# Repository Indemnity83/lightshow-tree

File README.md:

# lightshow-tree

Firmware and hardware notes for adapting a Member's Mark Pre-Lit Multicolor
Lightshow Tree to a Falcon differential output.

The first target retains the tree's factory power board, connector harness, and
30 vertical WS28xx data paths. Two Falcon differential pixel outputs carry the
1,020 vertical pixels, 510 each; two small on-board RS-485 receivers convert
them to the STC MCU's 3.3 V input level.

## Status

The pixel-output mapping is confirmed, and the two-channel receiver drives all
30 verticals from two Falcon outputs: a Falcon chase test runs cleanly across
the seam between verticals 15 and 16. The power limiter holds full white
at about 1.24 A from the factory 1.6 A supply. The star and a fourth output are
deferred (see the hardware plan).

| Target | Purpose |
| --- | --- |
| `blank` | Drives all 31 pixel-data pins low (WS28xx idle); safe first flash |
| `mapper` | Lights one of the 31 outputs dim red; the button steps to the next |
| `color-test` | Whole tree dim red, green, or blue; the button cycles the color |
| `demo` | Red/green/blue spiral bands; the button rotates them |
| `probe` | Reports activity and polarity on the three former radio pads |
| `receiver` | Two-channel Falcon receiver |

## Layout

- `docs/` — confirmed board mapping, open questions, and ISP procedure
- `include/` — board-level declarations
- `src/` — firmware source
- `scripts/` — local development helpers

## Toolchain

The project targets the STC8H8K64U (8051-compatible) MCU.

- [SDCC](https://sdcc.sourceforge.net/) compiles the firmware.
- [stc8prog](https://github.com/IOsetting/stc8prog) detects and flashes the MCU
  over UART on macOS.

Once both are installed:

```sh
make
make blank
make mapper
make receiver
make probe
make check-toolchain
make detect PORT=/dev/cu.usbserial-XXXX
make flash-receiver PORT=/dev/cu.usbserial-XXXX
make terminal PORT=/dev/cu.usbserial-XXXX
```

`make detect` is non-destructive. See `docs/isp.md` before running it.
Exit the serial terminal with `Ctrl-A`, then `\\`.

The local `tools/stc8prog/` checkout is ignored by Git. It is the default
flashing tool while developing on this Mac; a globally installed copy can be
selected with `make STC8PROG=stc8prog ...`.

See [the hardware plan](docs/hardware-plan.md) for the selected MAX3485 and
base-mounted RJ45 breakout modules, wiring, and Falcon pair selection.

## Falcon receiver bring-up

`make receiver` builds the RS-485 receiver firmware. It samples two MAX3485
`RXD` outputs at once: channel 1 on STC pin 27 / P3.6 (verticals 1–15) and
channel 2 on STC pin 29 / P4.1 (verticals 16–30). Each channel is one
510-pixel RGB Falcon output; this tree uses Falcon ports 29 and 30. The
firmware replays the frame in the confirmed clockwise order. Brightness is
set by the Falcon port; the firmware only scales a frame down if its
estimated draw would exceed the power supply budget.

Flash it only with each MAX3485 configured receive-only (`T` open, `EN` low or
open, `TXD` unconnected). Use `make flash-probe` first to confirm each pad
sees its own correctly polarized signal. The first valid capture emits
`frame: captured and replayed` on the UART. See `docs/receiver.md` for the
bring-up procedure, troubleshooting, and the sampling delay.

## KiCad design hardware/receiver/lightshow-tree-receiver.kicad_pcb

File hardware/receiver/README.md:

# Lightshow Tree Differential Receiver Daughterboard

This KiCad project will hold a small, castellated daughterboard installed on
the pads exposed by removing the factory PAN2110P0AA radio.  Its function is to
receive Falcon differential data feeds and deliver logic-level signals to the
existing STC8H8K64U.

The current KiCad design receives one feed.  The tree now needs two (510
pixels each, see `docs/hardware-plan.md`): channel 1 on GPIO 27 / pad 3 and
channel 2 on GPIO 29 / pad 1.  A future revision duplicates the receiver
circuit for the second channel.  The STC firmware then produces the 30
independent pixel outputs already proven on the factory board.

## Important constraint

The former radio pads provide a particularly useful three-wire interface.  The
factory firmware used the following three pins for the radio protocol, but our
replacement firmware can repurpose any one of them as a receiver-data GPIO:

| STC pin | Radio pin | Factory-radio function | Daughterboard use |
| --- | --- | --- | --- |
| 27 | 3 | data/SDA | channel 1 receiver data |
| 28 | 2 | clock/SCL | spare GPIO |
| 29 | 1 | chip select | channel 2 receiver data |

In addition, the radio footprint exposes its local 3.3 V and ground pads.  The
daughterboard will solder to exactly three factory pads: 3.3 V, ground, and the
chosen GPIO.  The factory radio's other pads are deliberately left unconnected
on the daughterboard.

The established UART pads remain useful only for development/debugging:

| Factory net | STC pin | Development use |
| --- | --- | --- |
| T2 / J1-2 | 19, P3.0 UART RX | ISP/programming |
| T3 / J1-6 | 20, P3.1 UART TX | optional debug output |
| 3.3 V test pad | 15, VCC | alternate measurement point |
| T4 | 17, GND | alternate measurement point |

The castellated edge therefore provides both the mechanical mounting and the
complete run-time electrical interface.  Revision 1 should still include
unpopulated debug pads for its input and ground, rather than a permanent wire
to T2/T3.

## First-revision functional blocks

1. Falcon differential-pair input connector/pads.
2. 3.3 V RS-485/RS-422 receiver with a valid high-speed logic output.
3. Logic connection to STC GPIO 27 (factory radio pin 3), with alternatives
   available on GPIO 28 and GPIO 29 if placement makes another pad preferable.
4. 3.3 V decoupling, input protection/termination option, and ground return.
5. Castellated mechanical edges, sized only after measuring the removed radio
   footprint and available clearances.

## Measurements still required before layout

- Exact PAN2110P0AA footprint dimensions and orientation on the factory PCB.
- Maximum safe daughterboard outline to the left of that footprint.
- Which Falcon differential pair/pairs will be connected and the physical
  connector/cable plan.
- Differential signalling details from the Falcon port: line rate, pair
  assignment, and whether a termination resistor is already present upstream.

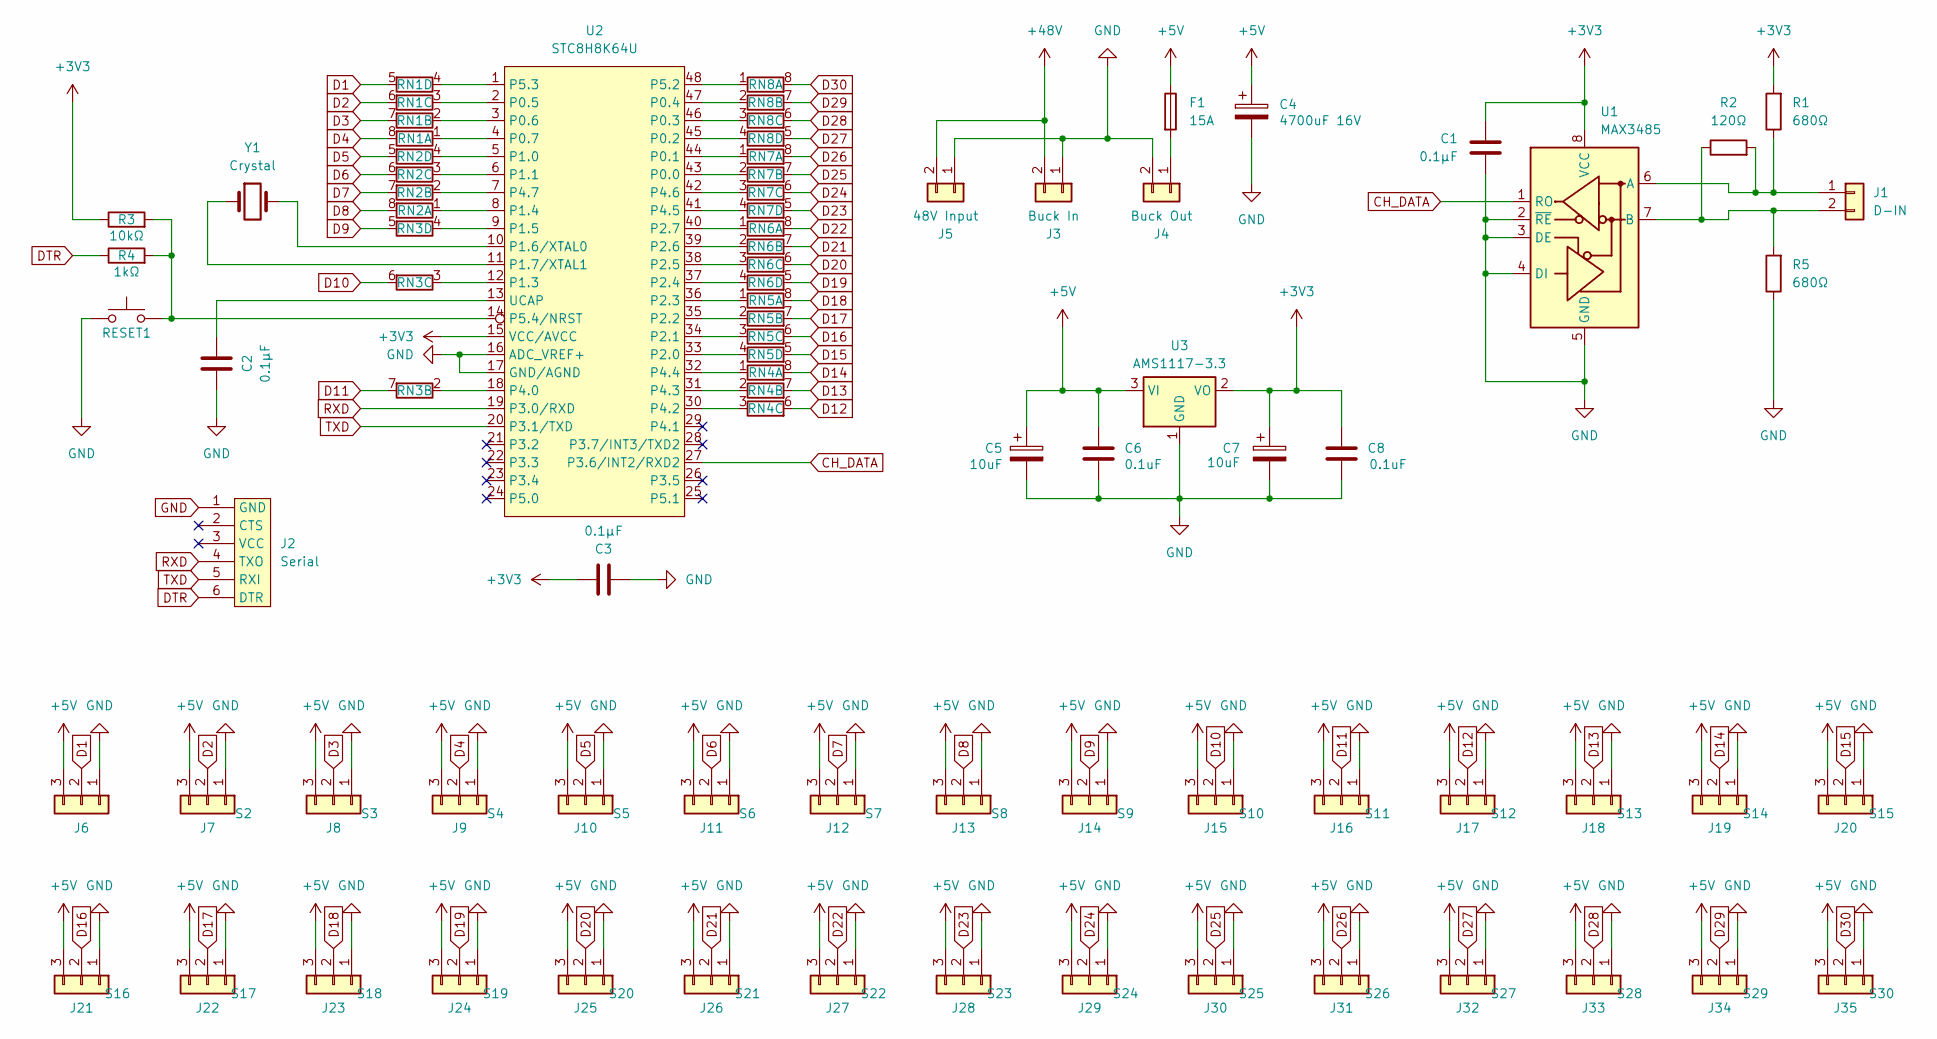
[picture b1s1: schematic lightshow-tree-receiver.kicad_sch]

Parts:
C1, C2, C3: 0.1µF; C_0805_2012Metric
C4: 4700uF 16V; CP_Radial_D16.0mm_P7.50mm
C5, C7: 10uF; CP_Radial_D5.0mm_P2.00mm
C6, C8: 0.1uF; C_0805_2012Metric
F1: 15A; Fuseholder_Blade_Mini_Keystone_3568
J1: D-IN; WirePads_1x02_P3.50mm_CAT5_6
J2: Serial; PinSocket_1x06_P2.54mm_Vertical
J3: Buck In; WirePads_1x02_P7.62mm_14AWG
J4: Buck Out; WirePads_1x02_P7.62mm_14AWG
J5: 48V Input; WirePads_1x02_P7.62mm_14AWG
J6: S1; WirePads_1x03_P2.20mm_FlatPixelWire
J7: S2; WirePads_1x03_P2.20mm_FlatPixelWire
J8: S3; WirePads_1x03_P2.20mm_FlatPixelWire
J9: S4; WirePads_1x03_P2.20mm_FlatPixelWire
J10: S5; WirePads_1x03_P2.20mm_FlatPixelWire
J11: S6; WirePads_1x03_P2.20mm_FlatPixelWire
J12: S7; WirePads_1x03_P2.20mm_FlatPixelWire
J13: S8; WirePads_1x03_P2.20mm_FlatPixelWire
J14: S9; WirePads_1x03_P2.20mm_FlatPixelWire
J15: S10; WirePads_1x03_P2.20mm_FlatPixelWire
J16: S11; WirePads_1x03_P2.20mm_FlatPixelWire
J17: S12; WirePads_1x03_P2.20mm_FlatPixelWire
J18: S13; WirePads_1x03_P2.20mm_FlatPixelWire
J19: S14; WirePads_1x03_P2.20mm_FlatPixelWire
J20: S15; WirePads_1x03_P2.20mm_FlatPixelWire
J21: S16; WirePads_1x03_P2.20mm_FlatPixelWire
J22: S17; WirePads_1x03_P2.20mm_FlatPixelWire
J23: S18; WirePads_1x03_P2.20mm_FlatPixelWire
J24: S19; WirePads_1x03_P2.20mm_FlatPixelWire
J25: S20; WirePads_1x03_P2.20mm_FlatPixelWire
J26: S21; WirePads_1x03_P2.20mm_FlatPixelWire
J27: S22; WirePads_1x03_P2.20mm_FlatPixelWire
J28: S23; WirePads_1x03_P2.20mm_FlatPixelWire
J29: S24; WirePads_1x03_P2.20mm_FlatPixelWire
J30: S25; WirePads_1x03_P2.20mm_FlatPixelWire
J31: S26; WirePads_1x03_P2.20mm_FlatPixelWire
J32: S27; WirePads_1x03_P2.20mm_FlatPixelWire
J33: S28; WirePads_1x03_P2.20mm_FlatPixelWire
J34: S29; WirePads_1x03_P2.20mm_FlatPixelWire
J35: S30; WirePads_1x03_P2.20mm_FlatPixelWire
R1, R5: 680Ω; R_0805_2012Metric
R2: 120Ω; R_0805_2012Metric
R3: 10kΩ; R_0805_2012Metric
R4: 1kΩ; R_0805_2012Metric
RESET1: SW_Push; SW_TH_Tactile_Omron_B3F-100x
RN1, RN2, RN3, RN4, RN5, RN6, RN7, RN8: R_Pack04_Split; R_Array_Concave_4x0603
U1: MAX3485; SOIC-8_3.9x4.9mm_P1.27mm
U2: STC8H8K64U; LQFP-48_7x7mm_P0.5mm
U3: AMS1117-3.3; SOT-223-3_TabPin2
Y1: Crystal; Crystal_SMD_3225-4Pin_3.2x2.5mm

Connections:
+3V3: C1.1, C3.1, C7.1, C8.1, R1.2, R3.1, U1.8 (VCC), U2.15 (VCC/AVCC), U3.2 (VO)
+5V: C4.1, C5.1, C6.1, F1.1, J6.3, J7.3, J8.3, J9.3, J10.3, J11.3, J12.3, J13.3, J14.3, J15.3, J16.3, J17.3, J18.3, J19.3, J20.3, J21.3, J22.3, J23.3, J24.3, J25.3, J26.3, J27.3, J28.3, J29.3, J30.3, J31.3, J32.3, J33.3, J34.3, J35.3, U3.3 (VI)
+48V: J3.2, J5.2
CH_DATA: U1.1 (RO), U2.27 (P3.6/INT2/RXD2)
D1: J6.2, RN1.5 (R4.2)
D2: J7.2, RN1.6 (R3.2)
D3: J8.2, RN1.7 (R2.2)
D4: J9.2, RN1.8 (R1.2)
D5: J10.2, RN2.5 (R4.2)
D6: J11.2, RN2.6 (R3.2)
D7: J12.2, RN2.7 (R2.2)
D8: J13.2, RN2.8 (R1.2)
D9: J14.2, RN3.5 (R4.2)
D10: J15.2, RN3.6 (R3.2)
D11: J16.2, RN3.7 (R2.2)
D12: J17.2, RN4.6 (R3.2)
D13: J18.2, RN4.7 (R2.2)
D14: J19.2, RN4.8 (R1.2)
D15: J20.2, RN5.5 (R4.2)
D16: J21.2, RN5.6 (R3.2)
D17: J22.2, RN5.7 (R2.2)
D18: J23.2, RN5.8 (R1.2)
D19: J24.2, RN6.5 (R4.2)
D20: J25.2, RN6.6 (R3.2)
D21: J26.2, RN6.7 (R2.2)
D22: J27.2, RN6.8 (R1.2)
D23: J28.2, RN7.5 (R4.2)
D24: J29.2, RN7.6 (R3.2)
D25: J30.2, RN7.7 (R2.2)
D26: J31.2, RN7.8 (R1.2)
D27: J32.2, RN8.5 (R4.2)
D28: J33.2, RN8.6 (R3.2)
D29: J34.2, RN8.7 (R2.2)
D30: J35.2, RN8.8 (R1.2)
DTR: J2.6 (DTR), R4.1
GND: C1.2, C2.2, C3.2, C4.2, C5.2, C6.2, C7.2, C8.2, J2.1 (GND), J3.1, J4.2, J5.1, J6.1, J7.1, J8.1, J9.1, J10.1, J11.1, J12.1, J13.1, J14.1, J15.1, J16.1, J17.1, J18.1, J19.1, J20.1, J21.1, J22.1, J23.1, J24.1, J25.1, J26.1, J27.1, J28.1, J29.1, J30.1, J31.1, J32.1, J33.1, J34.1, J35.1, R5.1, RESET1.1, U1.2 (~RE), U1.3 (DE), U1.4 (DI), U1.5 (GND), U2.16 (ADC_VREF+), U2.17 (GND/AGND), U3.1 (GND); also elsewhere on the board
unnamed: J1.1, R1.1, R2.2, U1.6 (A)
unnamed: J1.2, R2.1, R5.2, U1.7 (B)
unnamed: F1.2, J4.1
unnamed: RN1.1 (R1.1), U2.4 (P0.7)
unnamed: RN1.2 (R2.1), U2.3 (P0.6)
unnamed: RN1.3 (R3.1), U2.2 (P0.5)
unnamed: RN1.4 (R4.1), U2.1 (P5.3)
unnamed: RN2.1 (R1.1), U2.8 (P1.4)
unnamed: RN2.2 (R2.1), U2.7 (P4.7)
unnamed: RN2.3 (R3.1), U2.6 (P1.1)
unnamed: RN2.4 (R4.1), U2.5 (P1.0)
unnamed: RN3.2 (R2.1), U2.18 (P4.0)
unnamed: RN3.3 (R3.1), U2.12 (P1.3)
unnamed: RN3.4 (R4.1), U2.9 (P1.5)
unnamed: RN4.1 (R1.1), U2.32 (P4.4)
unnamed: RN4.2 (R2.1), U2.31 (P4.3)
unnamed: RN4.3 (R3.1), U2.30 (P4.2)
unnamed: RN5.1 (R1.1), U2.36 (P2.3)
unnamed: RN5.2 (R2.1), U2.35 (P2.2)
unnamed: RN5.3 (R3.1), U2.34 (P2.1)
unnamed: RN5.4 (R4.1), U2.33 (P2.0)
unnamed: RN6.1 (R1.1), U2.40 (P2.7)
unnamed: RN6.2 (R2.1), U2.39 (P2.6)
unnamed: RN6.3 (R3.1), U2.38 (P2.5)
unnamed: RN6.4 (R4.1), U2.37 (P2.4)
unnamed: RN7.1 (R1.1), U2.44 (P0.1)
unnamed: RN7.2 (R2.1), U2.43 (P0.0)
unnamed: RN7.3 (R3.1), U2.42 (P4.6)
unnamed: RN7.4 (R4.1), U2.41 (P4.5)
unnamed: RN8.1 (R1.1), U2.48 (P5.2)
unnamed: RN8.2 (R2.1), U2.47 (P0.4)
unnamed: RN8.3 (R3.1), U2.46 (P0.3)
unnamed: RN8.4 (R4.1), U2.45 (P0.2)
unnamed: U2.10 (P1.6/XTAL0), Y1.2
unnamed: U2.11 (P1.7/XTAL1), Y1.1
unnamed 71: R3.2, R4.2, RESET1.2, U2.14 (P5.4/NRST); also elsewhere on the board
unnamed: C2.1, U2.13 (UCAP)
RXD: J2.4 (TXO), U2.19 (P3.0/RXD)
TXD: J2.5 (RXI), U2.20 (P3.1/TXD)

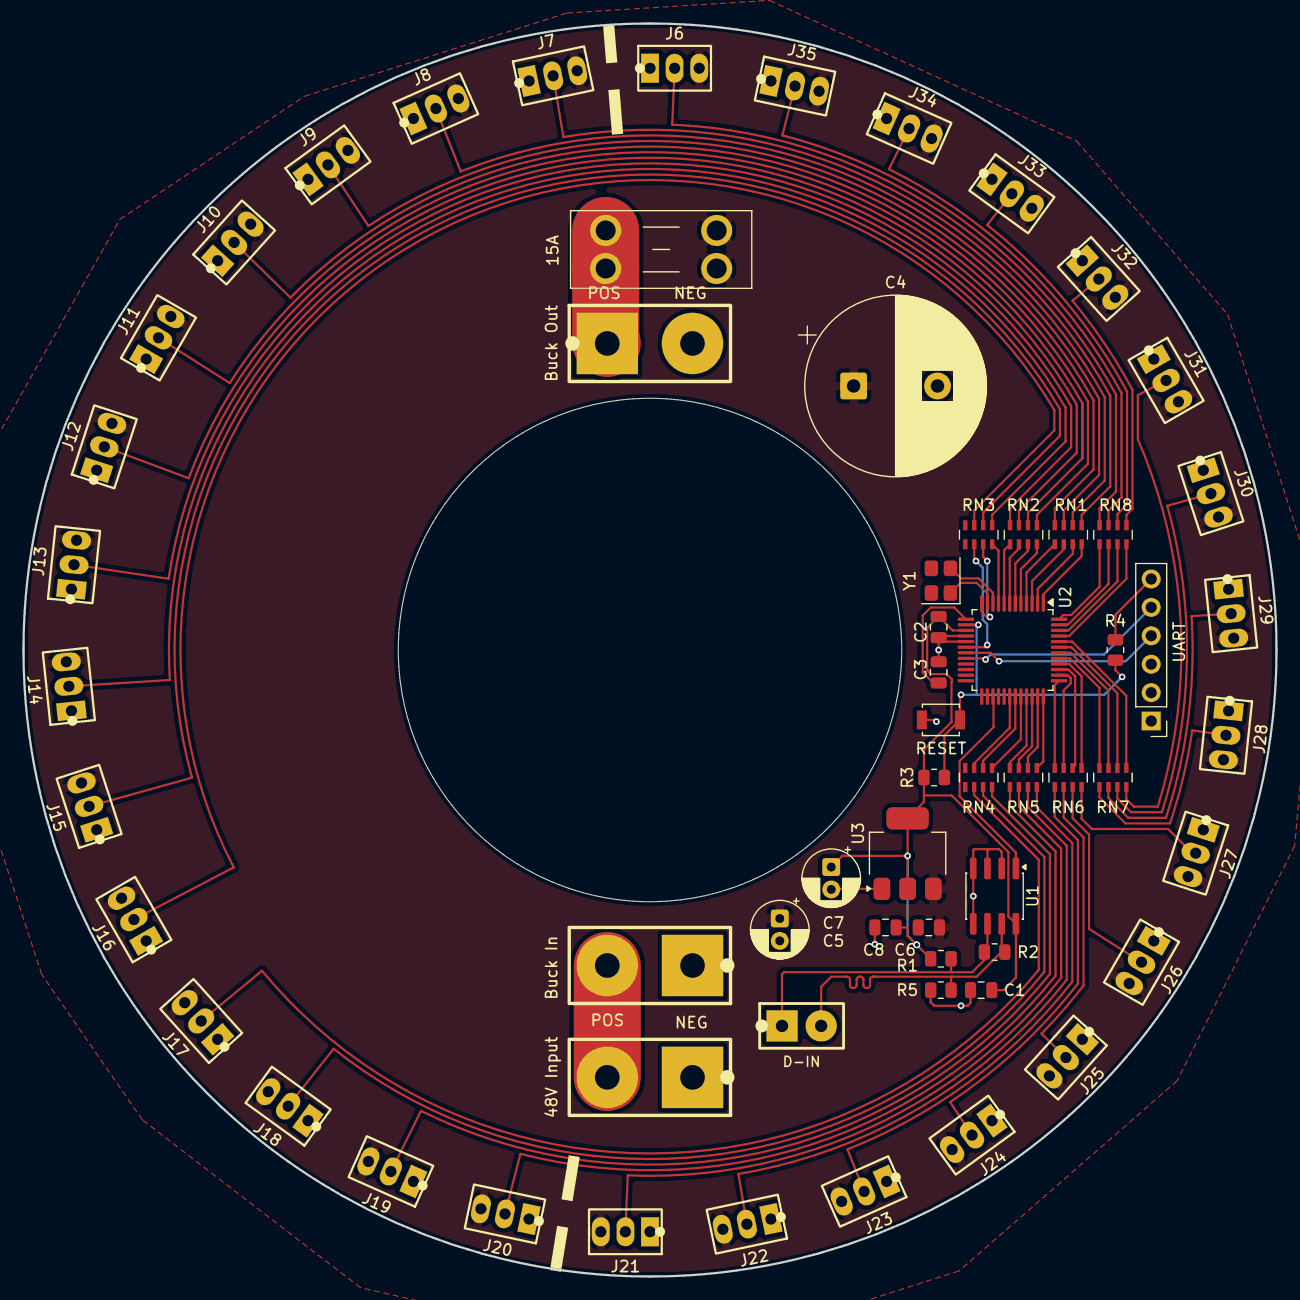
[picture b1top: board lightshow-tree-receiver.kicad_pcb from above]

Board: 2 copper layers, 112.0 x 112.0 mm, 62 parts (0 on the bottom side), 75 nets.

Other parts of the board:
RESET: SW_Push; SW_SPST_B3U-1000P

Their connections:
GND: RESET.1; also elsewhere on the board
unnamed 71: RESET.2; also elsewhere on the board
